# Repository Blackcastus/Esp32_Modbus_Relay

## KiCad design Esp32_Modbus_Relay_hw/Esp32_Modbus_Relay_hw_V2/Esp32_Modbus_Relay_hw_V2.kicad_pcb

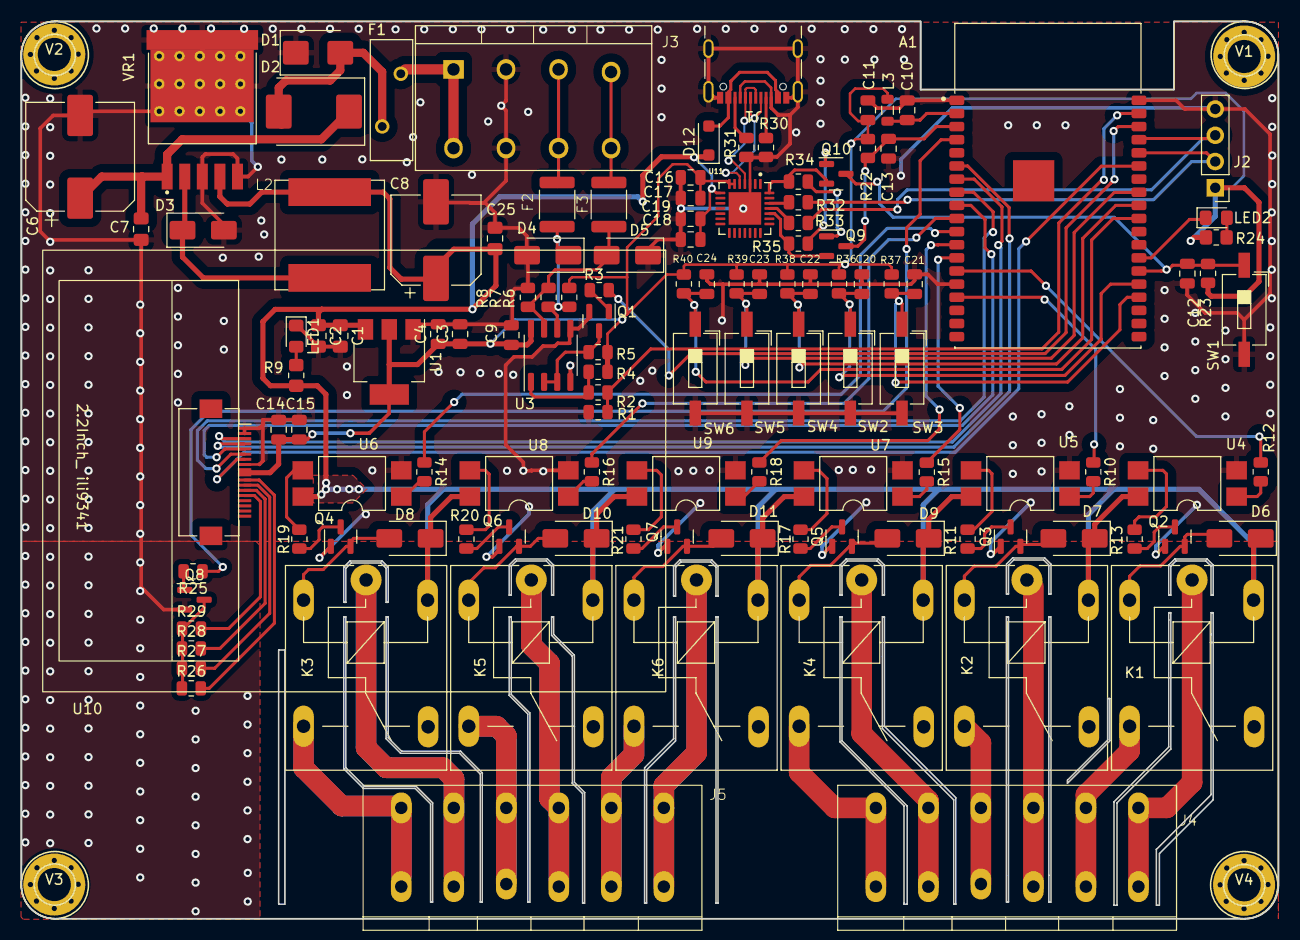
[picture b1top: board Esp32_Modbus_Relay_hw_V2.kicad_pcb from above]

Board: 2 copper layers, 121.6 x 86.8 mm, 126 parts (0 on the bottom side), 94 nets.

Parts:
A1: ESP32-WROVER-I; XCVR_ESP32-WROVER-I
C1, C7, C25: 100nF; C_0805_2012Metric_Pad1.18x1.45mm_HandSolder
C2: 10uF; C_0805_2012Metric_Pad1.18x1.45mm_HandSolder
C3, C14: 10uF; C_0805_2012Metric
C4, C9, C10, C12, C13, C15, C16, C17, C18, C19, C20, C21, C22, C23, C24: 100nF; C_0805_2012Metric
C6: 470uF/25V; CP_Elec_10x10
C8: 220uF/25V; CP_Elec_8x10.5
C11: 1uF; C_0805_2012Metric
D1: TVS; D_SMB
D2: ES3J_3A; D_SMC
D3: 1N5820; D_SMA
D4, D5: D_TVS; D_SMA
D6, D7, D8, D9, D10, D11: 1N4148; D_SMA
D12: 1N4007_T7; D_SOD-123F
F1: UF300_3A; Fuse_BelFuse_0ZRE0033FF_L11.4mm_W3.8mm
F2, F3: Fuse; Fuse_SMD_1812
J1: USB_C_Receptacle_USB2.0; USB_C_Receptacle_GCT_USB4105-xx-A_16P_TopMnt_Horizontal
J2: UART0_EXT; PinHeader_1x04_P2.54mm_Vertical
J3: header input; KF142_4P_5.08
J4, J5: Conn_01x06_Pin; KF142_6P_5.08
K1, K2, K3, K4, K5, K6: SRA-5VDC-CL; Relay_SPDT_SANYOU_SRD_Series_Form_C
L2: 33uH_2.9A; L_10x10
L3: 10uH; L_0805_2012Metric
LED1, LED2: RED; LED_0805_2012Metric_Pad1.15x1.40mm_HandSolder
Q1, Q8: 2SC1815-HF; SOT-23
Q2, Q3, Q4, Q5, Q6, Q7: 2SC1815/HF; SOT-23
Q9, Q10: S8050; SOT-23
R1, R4, R5, R22, R23, R36, R37, R38, R39, R40: 10K; R_0805_2012Metric
R2, R6, R8: 4.7K; R_0805_2012Metric
R3, R25: 2.2K; R_0805_2012Metric
R7: 120R; R_0805_2012Metric
R9: 2.2K; R_0805_2012Metric_Pad1.20x1.40mm_HandSolder
R10, R12, R14, R15, R16, R18: 330R; R_0805_2012Metric
R11, R13, R17, R19, R20, R21: 1k; R_0805_2012Metric
R24: 1K; R_0805_2012Metric_Pad1.20x1.40mm_HandSolder
R26, R27, R28, R29: 220R; R_0805_2012Metric
R30, R31: 5.1K; R_0805_2012Metric
R32, R33: 470R; R_0805_2012Metric
R34, R35: 10k; R_0805_2012Metric
SW1, SW2, SW3, SW4, SW5, SW6: SW_Push; SW_DIP_SPSTx01_Slide_6.7x4.1mm_W8.61mm_P2.54mm_LowProfile
U1: AMS1117-3.3; SOT-223-3_TabPin2
U3: MAX485; SO-8_3.9x4.9mm_P1.27mm
U4, U5, U6, U7, U8, U9: PC817; SMDIP-4_W9.53mm
U10: 2.2inch_TFT_ILI9341_SPI; TFT_ILI9341_2.2INCH
U11: CP2102-GM; CP2102
V1, V2, V3, V4: Vit
VR1: LM2596S-ADJ

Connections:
+3.3V: C3.1, C4.1, C9.2, C11.1, C14.1, C15.1, C16.1, C17.1, J2.1, L3.2, R4.1, R5.1, R6.1, R22.1, R23.1, R24.1, R36.1, R37.1, R38.1, R39.1, R40.1, U1.2 (VO), U3.8 (VCC), U10.9 (VCC), U10.10 (LEDA), U11.6 (VDD), U11.7 (REGIN)
+5V: C1.1, C2.1, C8.1, C18.1, C19.1, C25.1, D6.1 (K), D7.1 (K), D8.1 (K), D9.1 (K), D10.1 (K), D11.1 (K), D12.1 (K), K1.5, K2.5, K3.5, K4.5, K5.5, K6.5, L2.2, R9.1, U1.3 (VI), U4.4, U5.4, U6.4, U7.4, U8.4, U9.4, U11.8 (VBUS), VR1.4 (FB)
+12V: F1.1, J3.1
/BL1-: R26.2, U10.11 (LEDK1)
/BL2-: R27.2, U10.12 (LEDK2)
/BL3-: R28.2, U10.13 (LEDK3)
/BL4-: R29.2, U10.14 (LEDK4)
/BOOT: A1.25 (IO0), C12.1, Q10.3 (C), R23.2, SW1.1
/Blink: A1.26 (IO4), LED2.1 (K)
/COM1: J4.1, K1.1
/COM2: J4.3, K2.1
/COM3: J4.5, K4.1
/COM4: J5.1, K6.1
/COM5: J5.3, K5.1
/COM6: J5.5, K3.1
/CP_DTR: Q10.2 (E), R34.2, U11.28 (~DTR)
/CP_RST: Q9.2 (E), R35.2, U11.24 (~RST)
/CP_RXD: R33.2, U11.25 (RXD)
/CP_TXD: R32.2, U11.26 (TXD)
/DO1: A1.14 (IO12), R12.1
/DO2: A1.16 (IO13), R10.1
/DO3: A1.13 (IO14), R15.1
/DO4: A1.12 (IO27), R18.1
/DO5: A1.10 (IO25), R16.1
/DO6: A1.11 (IO26), R14.1
/DOWN: A1.23 (IO15), C21.1, R37.2, SW3.1
/EN: A1.3 (EN), C13.1, Q9.3 (C), R22.2
/LCD_BL: A1.4 (SENSOR_VP), R25.1
/LCD_CS0: A1.9 (IO33), U10.5 (CS)
/LCD_DC: A1.6 (IO34), U10.4 (D/C)
/LCD_MISO: A1.33 (IO21), U10.7 (SD0)
/LCD_MOSI: A1.8 (IO32), U10.6 (SDA)
/LCD_SCL: A1.7 (IO35), U10.3 (SCL)
/LEFT: A1.30 (IO18), C22.1, R38.2, SW4.1
/NO1: J4.2, K1.3
/NO2: J4.4, K2.3
/NO3: J4.6, K4.3
/NO4: J5.2, K6.3
/NO5: J5.4, K5.3
/NO6: J5.6, K3.e
/OK: A1.29 (IO5), C24.1, R40.2, SW6.1
/RIGHT: A1.31 (IO19), C23.1, R39.2, SW5.1
/RXD0: A1.34 (RXD0), J2.2, R32.1
/RXD1: A1.37 (IO23), R1.2, R2.1
/TXD0: A1.35 (TXD0), J2.3, R33.1
/TXD1: A1.36 (IO22), R3.1
/UP: A1.24 (IO2), C20.1, R36.2, SW2.1
/USB_D+: J1.A6 (D+), J1.B6 (D+), U11.4 (D+)
/USB_D-: J1.A7 (D-), J1.B7 (D-), U11.5 (D–)
A: F2.2, J3.3
B: F3.2, J3.4
GND: A1.1 (GND), A1.15 (GND), A1.38 (GND), C1.2, C2.2, C3.2, C4.2, C6.2, C7.2, C8.2, C9.1, C10.2, C11.2, C12.2, C13.2, C14.2, C15.2, C16.2, C17.2, C18.2, C19.2, C20.2, C21.2, C22.2, C23.2, C24.2, C25.2, D1.1 (A1), D3.2 (A), D4.2 (A2), D5.1 (A1), J1.A1 (GND), J1.A8 (SBU1), J1.A12 (GND), J1.B1 (GND), J1.B8 (SBU2), J1.B12 (GND), J1.S1 (SHIELD), J2.4, J3.2, LED1.1 (K), Q1.2 (E), Q2.1 (E), Q3.1 (E), Q4.1 (E), Q5.1 (E), Q6.1 (E), Q7.1 (E), Q8.2 (E), R1.1, R8.2, R30.1, R31.1, SW1.2, SW2.2, SW3.2, SW4.2, SW5.2, SW6.2, U1.1 (GND), U3.4 (DI), U3.5 (GND), U4.2, U5.2, U6.2, U7.2, U8.2, U9.2, U10.1 (GND), U10.2 (RESET), U10.8 (GND), U11.3 (GND), U11.29 (GND), VR1.3 (GND), VR1.5 (~ON/OFF), VR1.6 (GND)
unnamed: A1.2 (VDD3V3), C10.1, L3.1
unnamed: D1.2 (A2), D2.2 (A), F1.2
unnamed: C6.1, C7.1, D2.1 (K), VR1.1 (VIN)
unnamed: D3.1 (K), L2.1, VR1.2 (OUT)
unnamed: D4.1 (A1), F2.1, R6.2, R7.1, U3.6 (A)
unnamed: D5.2 (A2), F3.1, R7.2, R8.1, U3.7 (B)
unnamed: D6.2 (A), K1.2, Q2.2 (C)
unnamed: D7.2 (A), K2.2, Q3.2 (C)
unnamed: D8.2 (A), K3.2, Q4.2 (C)
unnamed: D9.2 (A), K4.2, Q5.2 (C)
unnamed: D10.2 (A), K5.2, Q6.2 (C)
unnamed: D11.2 (A), K6.2, Q7.2 (C)
unnamed: D12.2 (A), J1.A4 (VBUS), J1.A9 (VBUS), J1.B4 (VBUS), J1.B9 (VBUS)
unnamed: J1.A5 (CC1), R30.2
unnamed: J1.B5 (CC2), R31.2
unnamed: LED1.2 (A), R9.2
unnamed: LED2.2 (A), R24.2
unnamed: Q1.1 (B), R3.2
unnamed: Q1.3 (C), R5.2, U3.2 (~RE), U3.3 (DE)
unnamed: Q2.3 (B), R13.2
unnamed: Q3.3 (B), R11.2
unnamed: Q4.3 (B), R19.2
unnamed: Q5.3 (B), R17.2
unnamed: Q6.3 (B), R20.2
unnamed: Q7.3 (B), R21.2
unnamed: Q8.1 (B), R25.2
unnamed: Q8.3 (C), R26.1, R27.1, R28.1, R29.1
unnamed: Q9.1 (B), R34.1
unnamed: Q10.1 (B), R35.1
unnamed: R10.2, U5.1
unnamed: R11.1, U5.3
unnamed: R12.2, U4.1
unnamed: R13.1, U4.3
unnamed: R14.2, U6.1
unnamed: R15.2, U7.1
unnamed: R16.2, U8.1
unnamed: R17.1, U7.3
unnamed: R18.2, U9.1
unnamed: R19.1, U6.3
unnamed: R20.1, U8.3
unnamed: R21.1, U9.3
unnamed: R2.2, R4.2, U3.1 (RO)

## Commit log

2023-04-28 create project
2023-04-28 Block Power, Relay
2023-05-02 Finish version 01
2023-05-02 create Version 02
